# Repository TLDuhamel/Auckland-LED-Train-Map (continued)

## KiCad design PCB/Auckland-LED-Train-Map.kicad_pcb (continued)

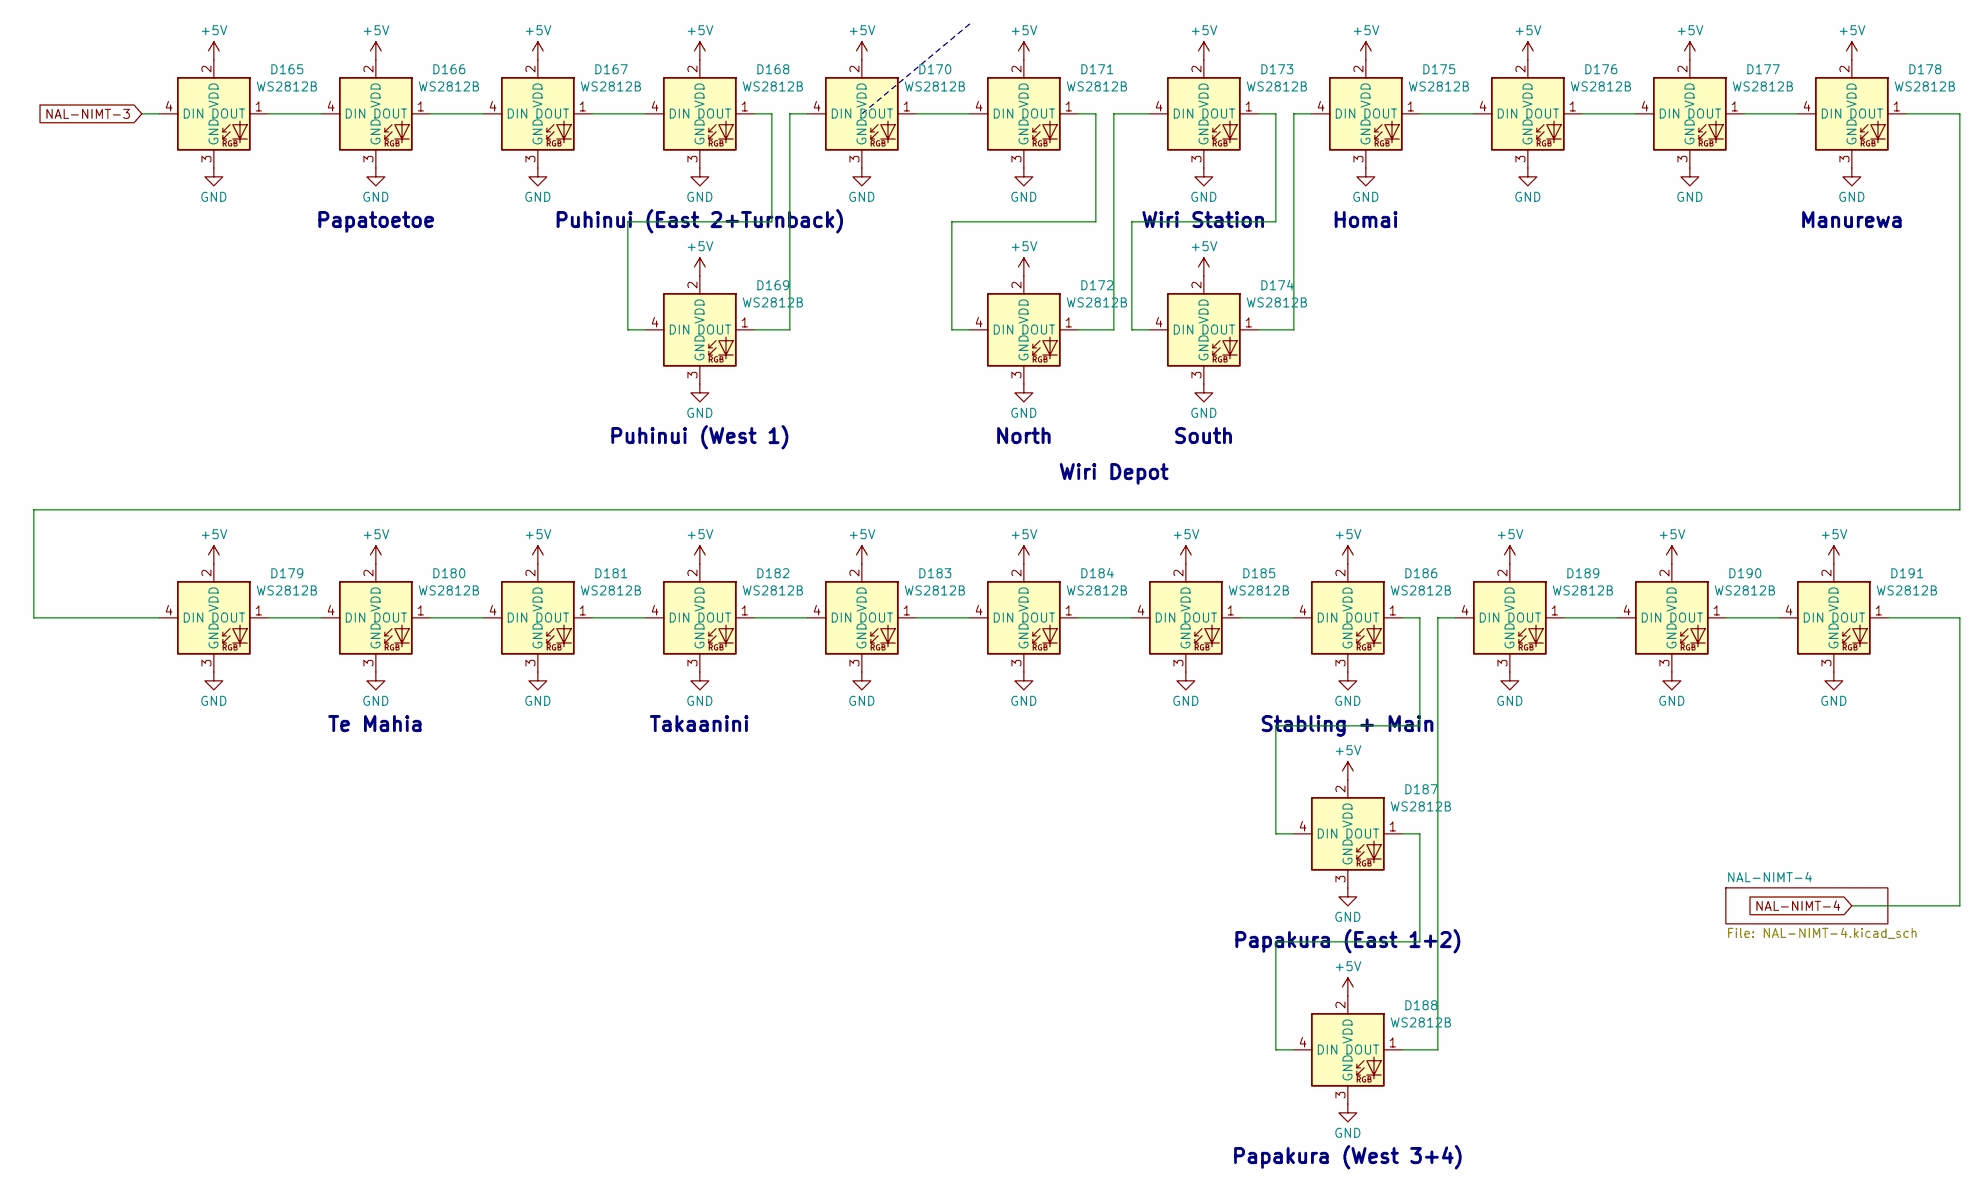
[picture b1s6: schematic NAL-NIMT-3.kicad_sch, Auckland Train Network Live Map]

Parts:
D165, D166, D167, D168, D169, D170, D171, D172, D173, D174, D175, D176, D177, D178, D179, D180, D181, D182, D183, D184, D185, D186, D187, D188, D189, D190, D191: WS2812B; LED-SMD_4P-L1.6-W1.5_XL-1615RGBC-WS2812B; LCSC C5349954

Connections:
+5V: D165.2 (VDD), D166.2 (VDD), D167.2 (VDD), D168.2 (VDD), D169.2 (VDD), D170.2 (VDD), D171.2 (VDD), D172.2 (VDD), D173.2 (VDD), D174.2 (VDD), D175.2 (VDD), D176.2 (VDD), D177.2 (VDD), D178.2 (VDD), D179.2 (VDD), D180.2 (VDD), D181.2 (VDD), D182.2 (VDD), D183.2 (VDD), D184.2 (VDD), D185.2 (VDD), D186.2 (VDD), D187.2 (VDD), D188.2 (VDD), D189.2 (VDD), D190.2 (VDD), D191.2 (VDD); also elsewhere on the board
GND: D165.3 (GND), D166.3 (GND), D167.3 (GND), D168.3 (GND), D169.3 (GND), D170.3 (GND), D171.3 (GND), D172.3 (GND), D173.3 (GND), D174.3 (GND), D175.3 (GND), D176.3 (GND), D177.3 (GND), D178.3 (GND), D179.3 (GND), D180.3 (GND), D181.3 (GND), D182.3 (GND), D183.3 (GND), D184.3 (GND), D185.3 (GND), D186.3 (GND), D187.3 (GND), D188.3 (GND), D189.3 (GND), D190.3 (GND), D191.3 (GND); also elsewhere on the board
NAL-NIMT-3: D165.4 (DIN); also elsewhere on the board
NAL-NIMT-4: D191.1 (DOUT); also elsewhere on the board
unnamed: D165.1 (DOUT), D166.4 (DIN)
unnamed: D166.1 (DOUT), D167.4 (DIN)
unnamed: D167.1 (DOUT), D168.4 (DIN)
unnamed: D168.1 (DOUT), D169.4 (DIN)
unnamed: D169.1 (DOUT), D170.4 (DIN)
unnamed: D170.1 (DOUT), D171.4 (DIN)
unnamed: D171.1 (DOUT), D172.4 (DIN)
unnamed: D172.1 (DOUT), D173.4 (DIN)
unnamed: D173.1 (DOUT), D174.4 (DIN)
unnamed: D174.1 (DOUT), D175.4 (DIN)
unnamed: D175.1 (DOUT), D176.4 (DIN)
unnamed: D176.1 (DOUT), D177.4 (DIN)
unnamed: D177.1 (DOUT), D178.4 (DIN)
unnamed: D178.1 (DOUT), D179.4 (DIN)
unnamed: D179.1 (DOUT), D180.4 (DIN)
unnamed: D180.1 (DOUT), D181.4 (DIN)
unnamed: D181.1 (DOUT), D182.4 (DIN)
unnamed: D182.1 (DOUT), D183.4 (DIN)
unnamed: D183.1 (DOUT), D184.4 (DIN)
unnamed: D184.1 (DOUT), D185.4 (DIN)
unnamed: D185.1 (DOUT), D186.4 (DIN)
unnamed: D186.1 (DOUT), D187.4 (DIN)
unnamed: D187.1 (DOUT), D188.4 (DIN)
unnamed: D188.1 (DOUT), D189.4 (DIN)
unnamed: D189.1 (DOUT), D190.4 (DIN)
unnamed: D190.1 (DOUT), D191.4 (DIN)

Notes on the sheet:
Homai
Manurewa
Stabling + Main
North
Puhinui (West 1)
Wiri Depot
Te Mahia
Papakura (West 3+4)
South
Takaanini
Puhinui (East 2+Turnback)
Wiri Station
Papatoetoe
Papakura (East 1+2)

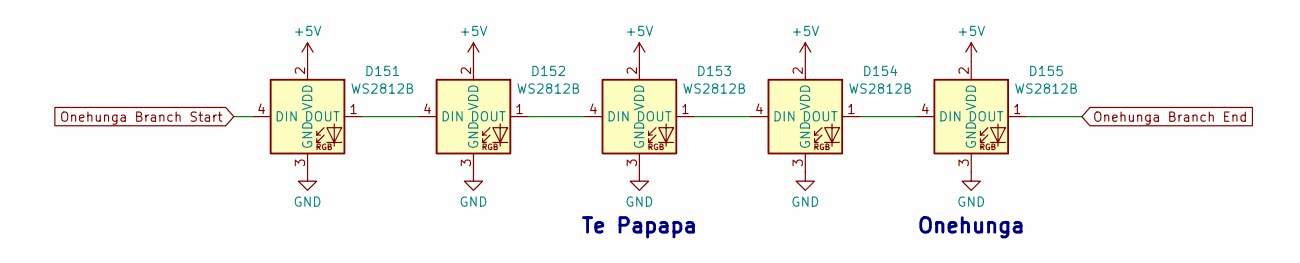
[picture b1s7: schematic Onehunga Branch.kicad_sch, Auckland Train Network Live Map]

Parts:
D151, D152, D153, D154, D155: WS2812B; LED-SMD_4P-L1.6-W1.5_XL-1615RGBC-WS2812B; LCSC C5349954

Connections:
+5V: D151.2 (VDD), D152.2 (VDD), D153.2 (VDD), D154.2 (VDD), D155.2 (VDD); also elsewhere on the board
GND: D151.3 (GND), D152.3 (GND), D153.3 (GND), D154.3 (GND), D155.3 (GND); also elsewhere on the board
unnamed: D151.1 (DOUT), D152.4 (DIN)
unnamed: D152.1 (DOUT), D153.4 (DIN)
unnamed: D153.1 (DOUT), D154.4 (DIN)
unnamed: D154.1 (DOUT), D155.4 (DIN)
Onehunga Branch End: D155.1 (DOUT); also elsewhere on the board
Onehunga Branch Start: D151.4 (DIN); also elsewhere on the board

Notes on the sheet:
Te Papapa
Onehunga

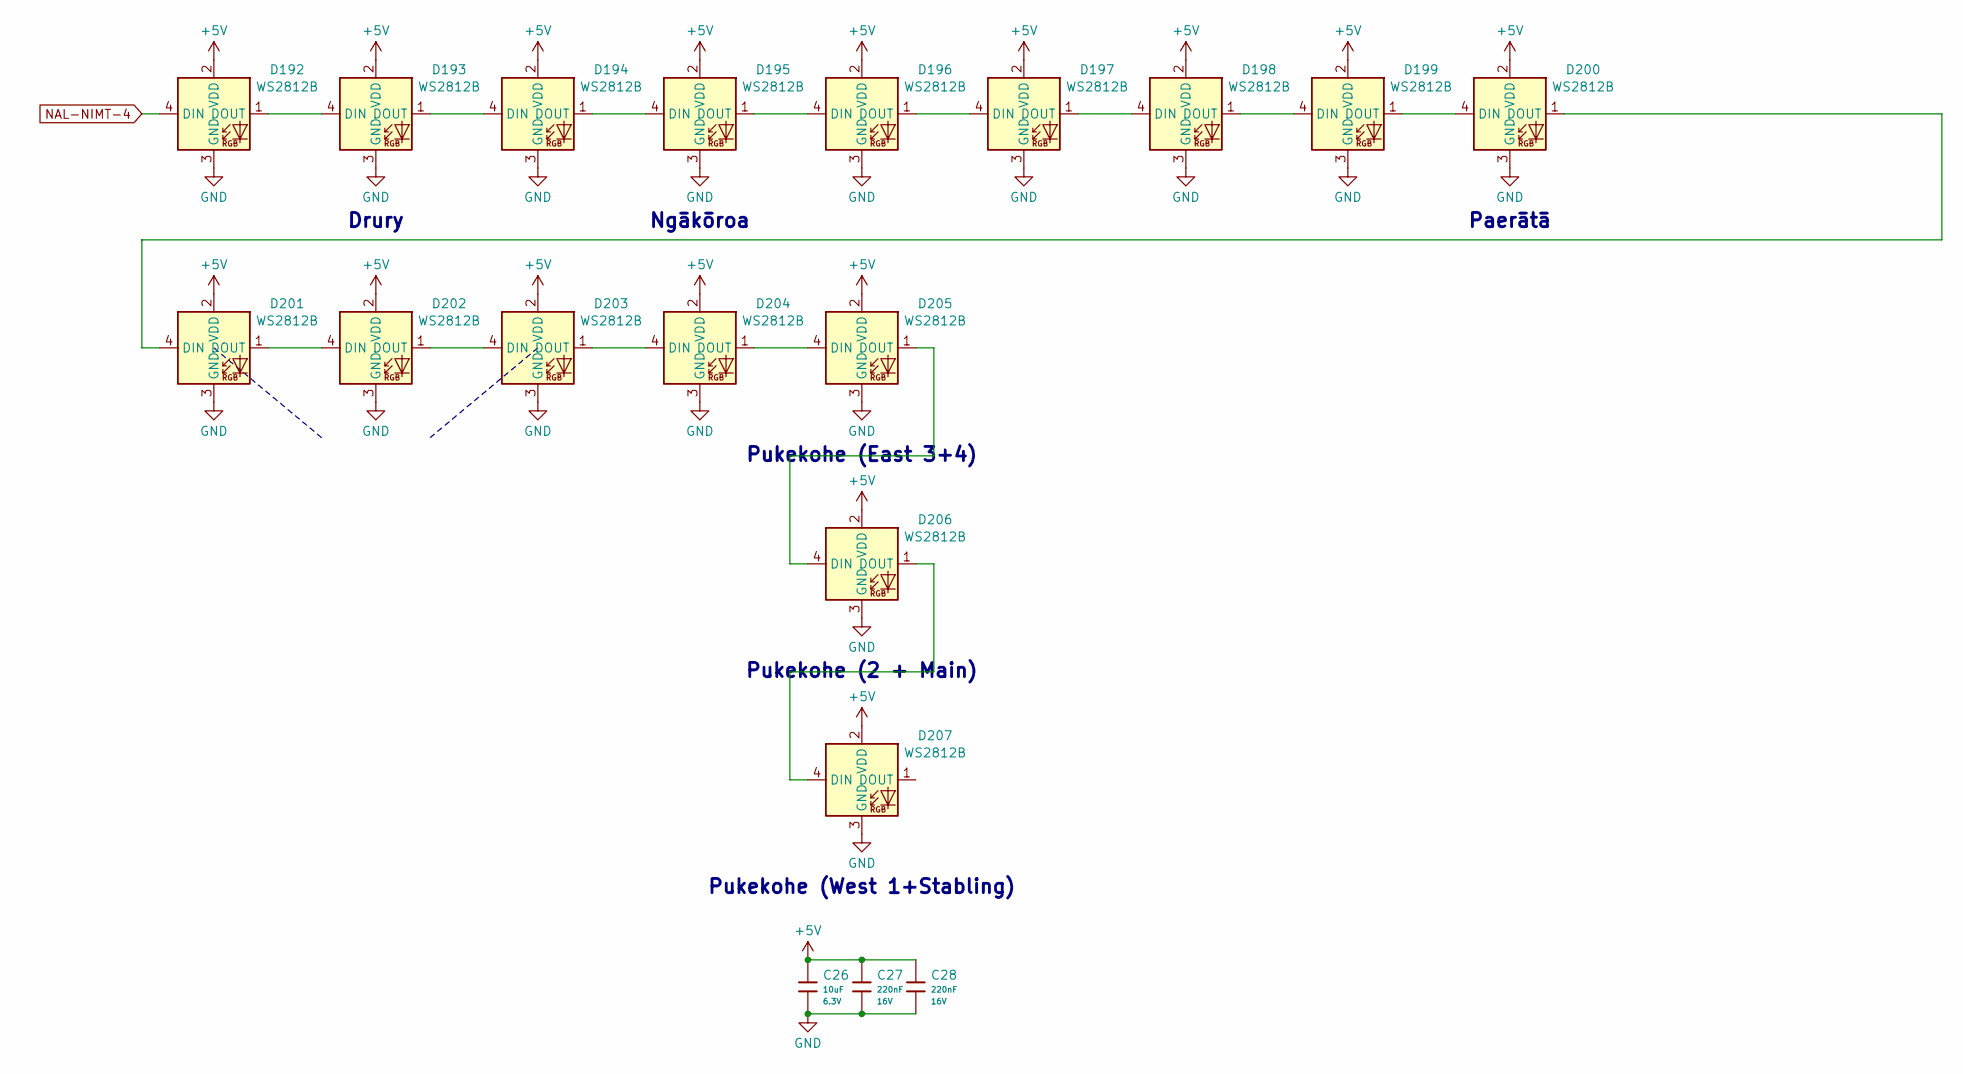
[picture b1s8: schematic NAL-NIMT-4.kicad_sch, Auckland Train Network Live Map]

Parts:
C26: 10uF; C_0402; Voltage Rated 6.3V; Tolerance ±20%; Part CL05A106MQ5NUNC; LCSC C15525
C27, C28: 220nF; C_0402; Voltage Rated 16V; Tolerance ±10%; Part CL05B224KO5NNNC; LCSC C16772
D192, D193, D194, D195, D196, D197, D198, D199, D200, D201, D202, D203, D204, D205, D206, D207: WS2812B; LED-SMD_4P-L1.6-W1.5_XL-1615RGBC-WS2812B; LCSC C5349954

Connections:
+5V: C26.1, C27.1, C28.1, D192.2 (VDD), D193.2 (VDD), D194.2 (VDD), D195.2 (VDD), D196.2 (VDD), D197.2 (VDD), D198.2 (VDD), D199.2 (VDD), D200.2 (VDD), D201.2 (VDD), D202.2 (VDD), D203.2 (VDD), D204.2 (VDD), D205.2 (VDD), D206.2 (VDD), D207.2 (VDD); also elsewhere on the board
GND: C26.2, C27.2, C28.2, D192.3 (GND), D193.3 (GND), D194.3 (GND), D195.3 (GND), D196.3 (GND), D197.3 (GND), D198.3 (GND), D199.3 (GND), D200.3 (GND), D201.3 (GND), D202.3 (GND), D203.3 (GND), D204.3 (GND), D205.3 (GND), D206.3 (GND), D207.3 (GND); also elsewhere on the board
NAL-NIMT-4: D192.4 (DIN); also elsewhere on the board
unnamed: D192.1 (DOUT), D193.4 (DIN)
unnamed: D193.1 (DOUT), D194.4 (DIN)
unnamed: D194.1 (DOUT), D195.4 (DIN)
unnamed: D195.1 (DOUT), D196.4 (DIN)
unnamed: D196.1 (DOUT), D197.4 (DIN)
unnamed: D197.1 (DOUT), D198.4 (DIN)
unnamed: D198.1 (DOUT), D199.4 (DIN)
unnamed: D199.1 (DOUT), D200.4 (DIN)
unnamed: D200.1 (DOUT), D201.4 (DIN)
unnamed: D201.1 (DOUT), D202.4 (DIN)
unnamed: D202.1 (DOUT), D203.4 (DIN)
unnamed: D203.1 (DOUT), D204.4 (DIN)
unnamed: D204.1 (DOUT), D205.4 (DIN)
unnamed: D205.1 (DOUT), D206.4 (DIN)
unnamed: D206.1 (DOUT), D207.4 (DIN)

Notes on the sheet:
Paerātā
Drury
Pukekohe (2 + Main)
Pukekohe (East 3+4)
Ngākōroa
Pukekohe (West 1+Stabling)

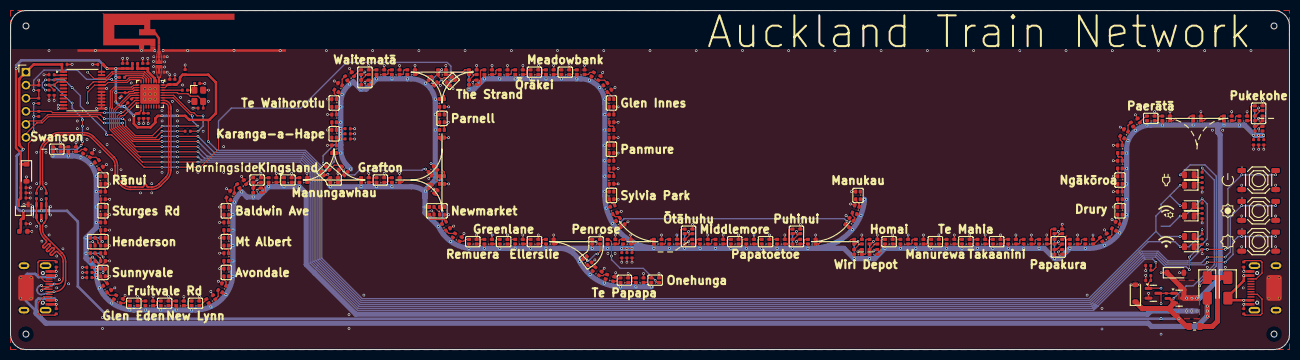
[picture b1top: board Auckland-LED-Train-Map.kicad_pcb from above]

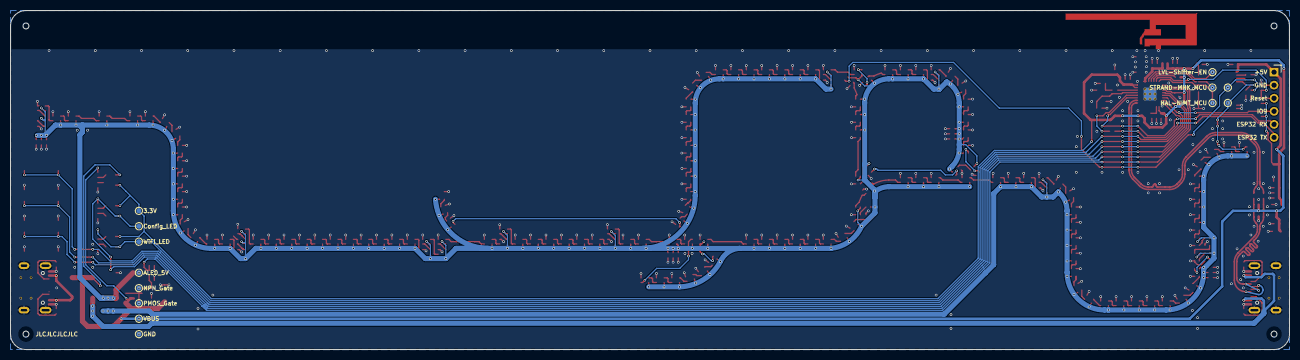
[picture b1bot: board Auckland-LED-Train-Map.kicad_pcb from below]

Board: 2 copper layers, 249.0 x 66.0 mm, 262 parts (14 on the bottom side), 200 nets.

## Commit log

2025-04-13 Long Version Checkpoint
2025-04-14 PCB Checkpoint
2025-04-15 Exclude JLCPCB production outputs from git
2025-04-15 - Remove JLCPCB Outputs - V1 RC1
2025-04-16 - V1 RC2 - Add icons
2025-04-16 Remove Empty Schematic
2025-04-27 - Add Readme - V1 RC3 PCB - Tidy up Schematic - Add Datasheets
2025-04-27 Fix image links in README.md
2025-04-27 Add Schematic to README
2025-04-28 Fix charlieplexed LEDs D10 and D11
2025-04-28 Add changes suggested from reddit
2025-05-15 Final tweaks for V1.0.0
2025-05-15 Fix U3 Footprint
2025-05-22 - Alpha V1.0.0 Firmware - Fix V1.0.0 spelling mistakes
2025-05-25 Refactor WiFi network handling and add button debouncing functionality
2025-05-26 Implement status LED task, add gamma correction, update clang-format settings
2025-05-29 Enhance LED control and time synchronization features; update JSON parsing and server handling
2025-05-31 Refactor status LED management and enhance WiFi connection reliability; increase timeout and set transmission power
2025-06-06 Add initial web installer for Auckland LED Rail Map
    - Created HTML interface for flashing and configuring the device.
    - Added manifest file for firmware installation.
    - Included binary firmware file for the device.
    - Added support for wifi-improv to the firmware
2025-06-06 Add GitHub Actions firmware deployment
2025-06-06 Fix bug if there are no wifi networks saved
2025-06-06 remove .bin update to 1.0.1
2025-06-06 Fix deployment script to create specific directory for Auckland LED Rail Map and update firmware handling
2025-06-06 Update firmware version display and fetch from manifest
2025-06-16 Auckland-V1.1-PCB (#2)
2025-06-16 Update firmware version to 1.0.2 and enhance server URL handling
2025-06-16 Add 3d printed stand and instructions
2025-06-16 Update firmware version to 1.0.3 and add CDC RX event handling
2025-06-23 V1.1.0 PCB
2025-06-28 Add support for V1.1.0 firmware
2025-06-28 Firmware deployment bugfix
2025-06-28 Firmware deployment bugfix 2
2025-06-28 Refactor deployment workflow so it no longer needs two jobs
2025-06-29 Update to meet OSHWA Certification
2025-06-30 Add factory test mode and improve brightness handling
    - Introduced factory test mode with LED color cycling for diagnostics.
    - Enhanced brightness management by saving and retrieving brightness settings using preferences.
    - Updated platformio.ini to include factory test environment.
2025-07-28 V1.1.1
2025-10-16 Add toggle for NIS train visibility when press both brightness buttons.
2026-03-15 local server as first option
2026-03-16 Add onrender backend server as first choice
2026-03-16 Log each server connection
